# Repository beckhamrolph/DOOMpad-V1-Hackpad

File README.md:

# DOOMpad-V1-Hackpad
This repository holds the information regarding my Hackpad submission.

# Inspiration
I have seen the trend of downloading a simplified version of the popular DOOM game on unconventional objects. I decided I would like to continue this trend by creating a Hackpad to run it aswell. 
# Challenges
The game DOOM was not originally meant to run on a microcontroller such as the XIAO. Therefore the code needs a massive overhaul to work with this sort of interface. Luckily, this project has been done with similar boards such as the original RP2040. Some minor re-working of the code should allow the game to run.
# Specifications
BOM:
- 9x Cherry MX Switches
- 1x Xiao RP2040
- 9x Blank DSA Keycaps
- 4x M3x16 Bolt
- 4x M3 Heatset
- 1x 0.91 inch OLED display

Others:
- Top_plate.stl
- Bottom_plate.stl
- DOOM Firmware

Schematic            |  PCB         |   Case
:-------------------------:|:-------------------------:|:-------------------------:|
    |    |

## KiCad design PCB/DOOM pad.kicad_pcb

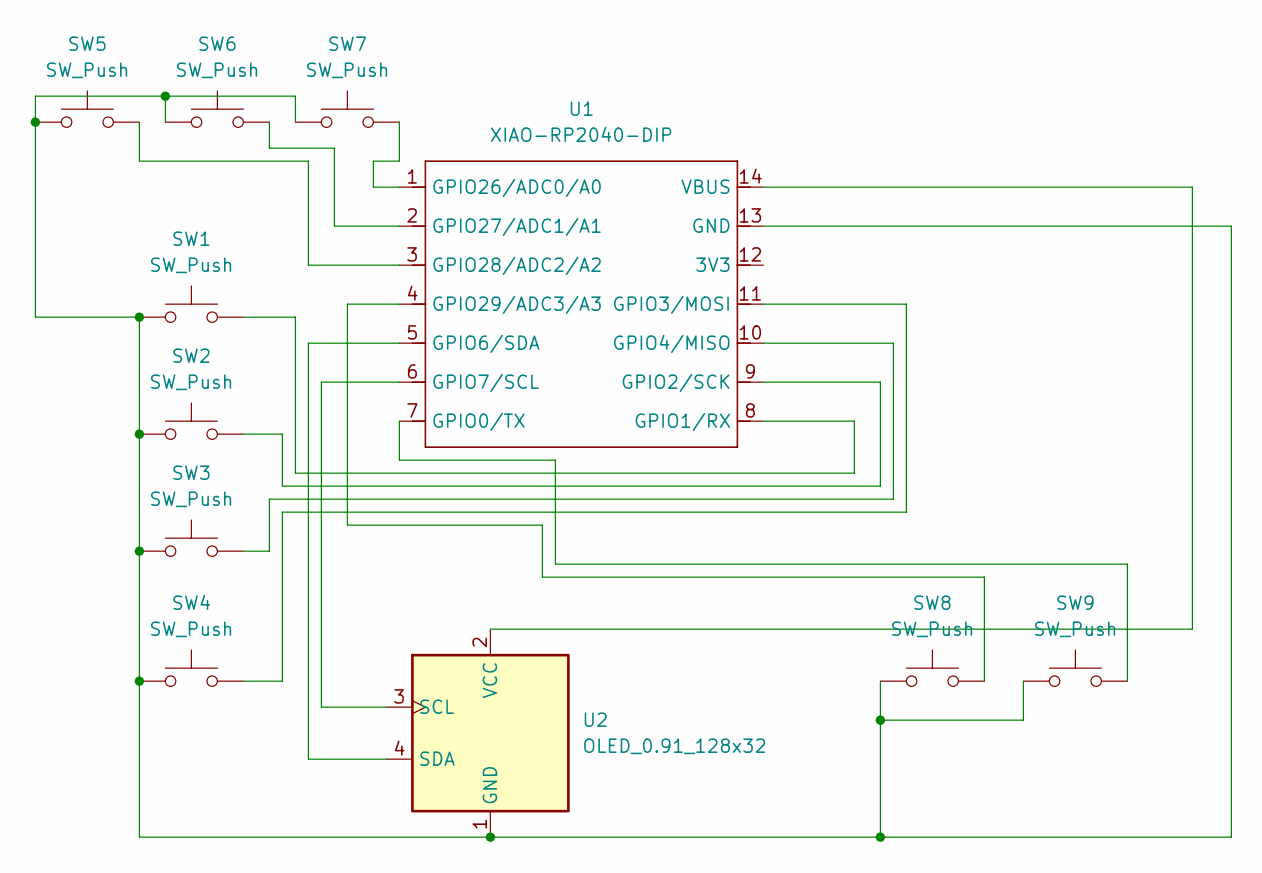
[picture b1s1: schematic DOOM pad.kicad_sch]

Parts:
SW1, SW2, SW3, SW4, SW5, SW6, SW7, SW8, SW9: SW_Push; SW_Cherry_MX_1.00u_PCB
U1: XIAO-RP2040-DIP; MCU_Seeed_ESP32C3
U2: OLED_0.91_128x32; SSD1306-0.91-OLED-4pin-128x32

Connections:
unnamed: SW1.1, SW2.1, SW3.1, SW4.1, SW5.1, SW6.1, SW7.1, SW8.1, SW9.1, U1.13 (GND), U2.1 (GND)
unnamed: SW9.2, U1.7 (GPIO0/TX)
unnamed: SW1.2, U1.8 (GPIO1/RX)
unnamed: SW2.2, U1.9 (GPIO2/SCK)
unnamed: SW4.2, U1.11 (GPIO3/MOSI)
unnamed: SW3.2, U1.10 (GPIO4/MISO)
unnamed: U1.5 (GPIO6/SDA), U2.4 (SDA)
unnamed: U1.6 (GPIO7/SCL), U2.3 (SCL)
unnamed: SW7.2, U1.1 (GPIO26/ADC0/A0)
unnamed: SW6.2, U1.2 (GPIO27/ADC1/A1)
unnamed: SW5.2, U1.3 (GPIO28/ADC2/A2)
unnamed: SW8.2, U1.4 (GPIO29/ADC3/A3)
unnamed: U1.14 (VBUS), U2.2 (VCC)

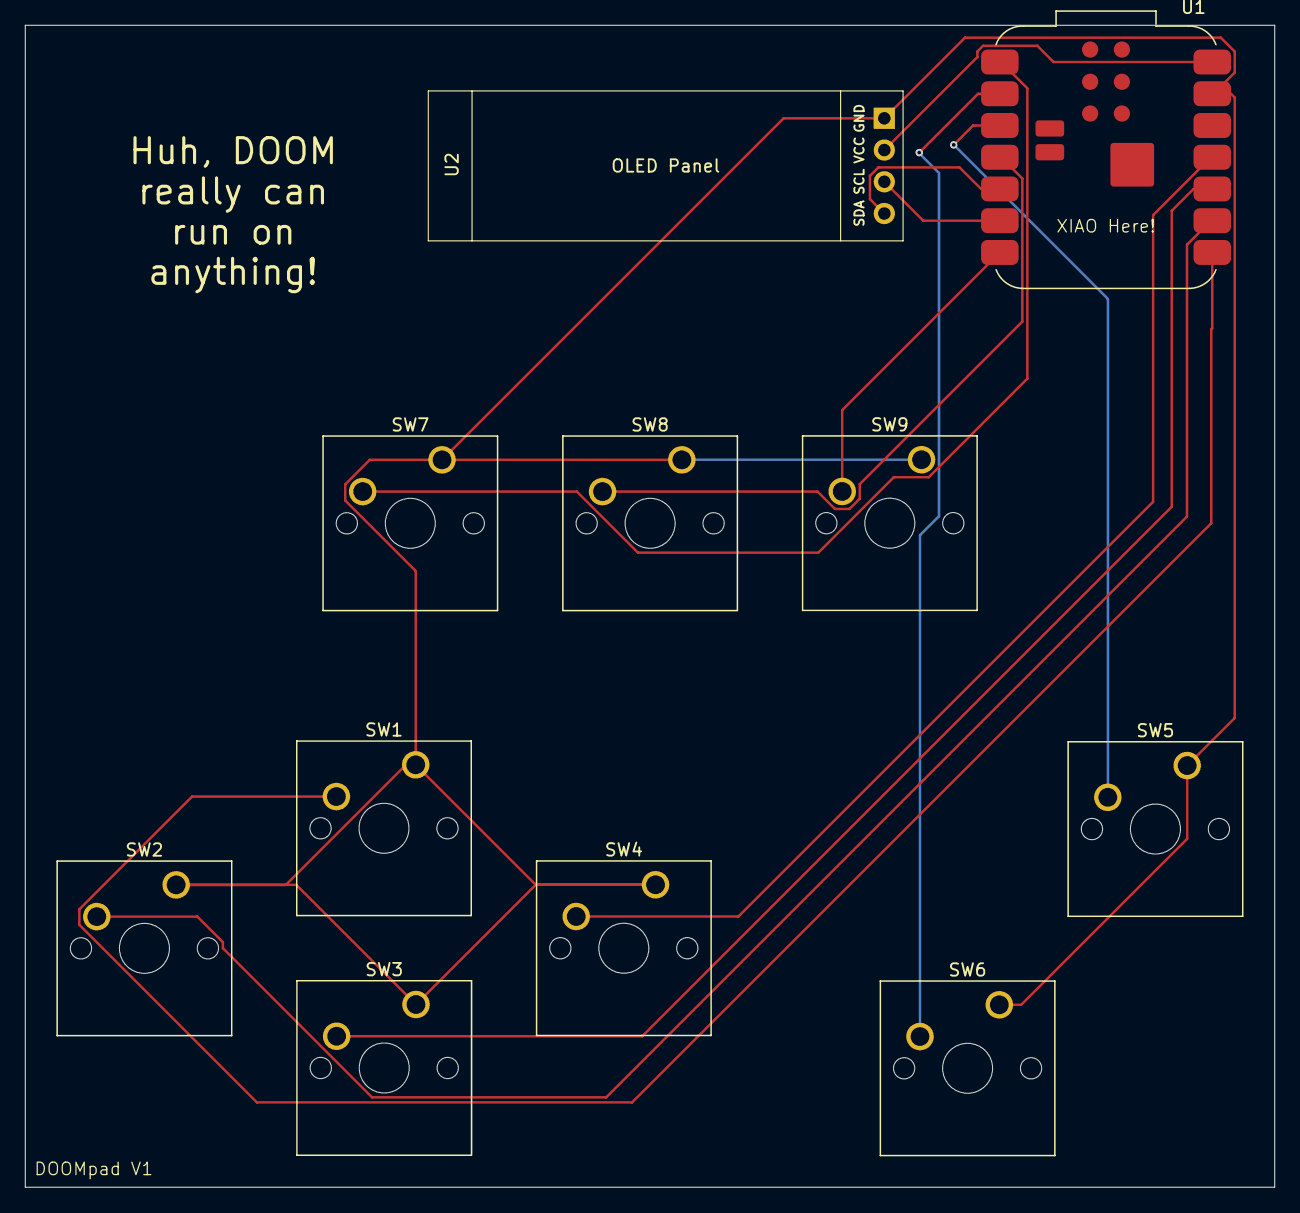
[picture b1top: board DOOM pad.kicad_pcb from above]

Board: 2 copper layers, 100.0 x 93.0 mm, 11 parts (0 on the bottom side), 13 nets.

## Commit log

2026-01-09 README.md
2026-01-19 PCB files
2026-01-19 CAD file
2026-01-19 Move to folder
2026-01-19 Set into file
2026-01-19 Set into folder
